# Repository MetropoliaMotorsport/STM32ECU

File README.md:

# ECU for Metropolia Motorsport Team

## Introduction
ECU project is meant to be used in the HPF24 and future cars. 
The project should provide a stable platform for the future development.
## Table of Contents
- [Installation](#installation)
- [Usage](#usage)
- [Contributing](#contributing)
- [Work Rules](##workrules)
- [Changelog](#changelog)
- [License](#license)
- [Acknowledgments](#acknowledgments)
- [Contact](#contact)

## Installation
Clone the project. And import it into the stm32 ide work.
Then build it and upload it to the car ECU using ST-Link.

## Usage
How to use the ECU, with examples.

## Contributing
All development should be done in the `dev` branch.
Create your own branch with your name for the purpose of experimenting and testing.

### Work Rules
1. **Development Branch:** All development should be in the `dev` branch.
2. **Main Branch:** Only working and tested solutions can be merged into `main`.
3. **Experimentation:** For experimenting, create your own branch with your name. You can also use it for development, but changes should be merged to the `dev` first.

## Changelog
History of significant changes.

## License
GPL 3.0 - License

## Acknowledgments
Credits to team members and contributors.

## Contact
Contact information for queries or support.

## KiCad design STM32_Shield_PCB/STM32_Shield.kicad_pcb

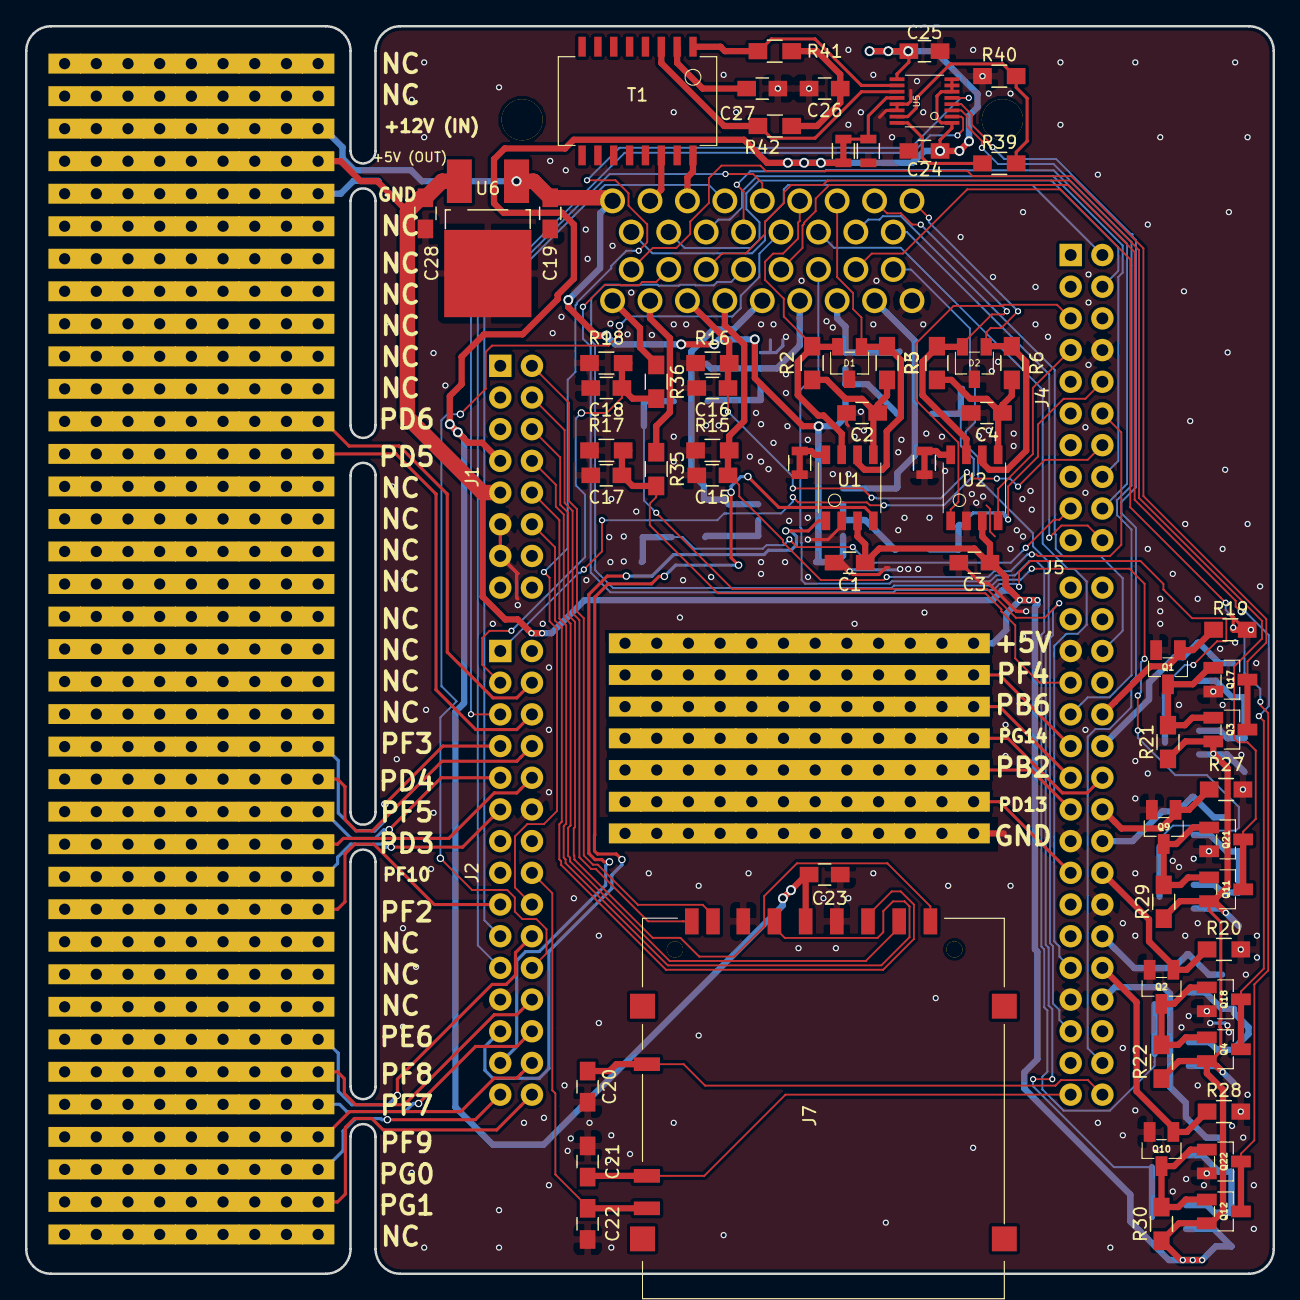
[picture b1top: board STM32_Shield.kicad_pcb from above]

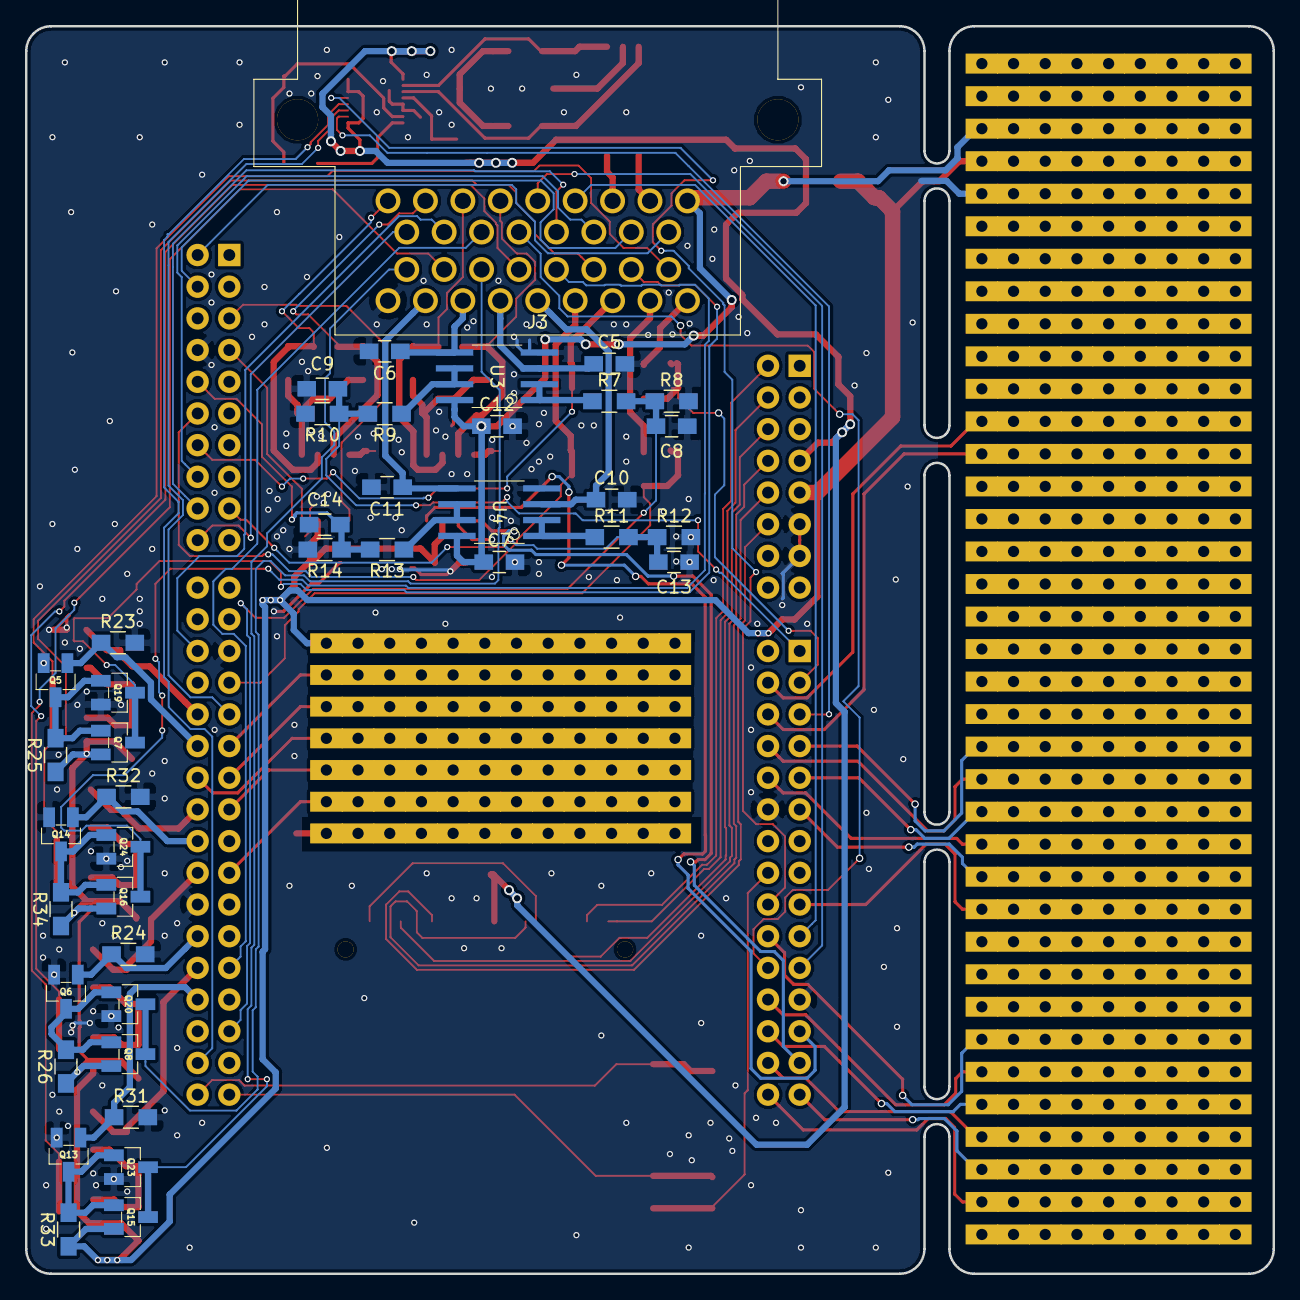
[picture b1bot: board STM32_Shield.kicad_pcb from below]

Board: 2 copper layers, 100.0 x 100.0 mm, 153 parts (41 on the bottom side), 109 nets.

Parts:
C1, C3, C7, C12, C20, C21, C22, C23, C24, C25, C26, C27, C28: 100nF; C_0805_HandSoldering
C2, C4, C5, C6, C8, C9, C10, C11, C13, C14, C15, C16, C17, C18: 4.7nF; C_0805_HandSoldering
C19: 330nF; C_0805_HandSoldering
D1, D2: ESDCAN24-2BLY
J1: Conn_02x08_Odd_Even; 2x08
J2: Conn_02x15_Odd_Even; 2x15
J3: Conn_01x34; SUPERSEAL_34POS
J4: Conn_02x10_Odd_Even; 2x10
J5: Conn_02x17_Odd_Even; 2x17
J6, J15, J16, J17, J18, J19, J20: stripboard_longer
J7: DM1AA
J8, J9, J10, J11, J12, J13, J14, J21, J22, J23, J24, J25, J26, J27, J28, J29, J30, J31, J32, J33, J34, J35, J36, J37, J38, J39, J40, J41, J42, J43, J44, J45, J46, J47, J48, J49, J52: stripboard
Q1, Q2, Q5, Q6, Q9, Q10, Q13, Q14, Q17, Q18, Q19, Q20, Q21, Q22, Q23, Q24: Q_NMOS_GSD; SOT-23
Q3, Q4, Q7, Q8, Q11, Q12, Q15, Q16: Q_PMOS_GSD; SOT-23
R1, R4: 0; jumper
R2, R3, R5, R6, R41, R42: 60; R_0805_HandSoldering
R7, R9, R11, R13: 1.74K; R_0805_HandSoldering
R8, R10, R12, R14, R19, R20, R23, R24, R27, R28, R31, R32: 3.3K; R_0805_HandSoldering
R15, R16: 270; R_0805_HandSoldering
R17, R18, R35, R36: ?; R_0805_HandSoldering
R21, R22, R25, R26, R29, R30, R33, R34: 5.1K; R_0805_HandSoldering
R37: R; jumper
R38: R; R_0805
R39, R40: 1K; R_0805_HandSoldering
T1: HALO_TG110_AEX50N5LF; HALO_N5
U1, U2: TJA1050
U3, U4: LM358; SOIC-8
U5: LTC6820; ltc6820
U6: L7805; TO-252-2_Rectifier

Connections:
+3V3: C23.2, C24.2, C25.2, J1.7, J7.4, R37.1, U5.1, U5.6, U5.7, U5.8, U5.9
+5V: C1.1, C3.1, C28.1, J1.9, J6.1, J12.1, Q3.2, Q4.2, Q7.2, Q8.2, Q11.2, Q12.2, Q15.2, Q16.2, R21.1, R22.1, R25.1, R26.1, R29.1, R30.1, R33.1, R34.1, U1.3, U2.3, U6.3
+12V: C7.1, C12.1, C19.1, J3.26, J10.1, U3.8, U4.8, U6.1
AI0: C5.1, J3.6, U3.3
AI1: C6.1, J3.7, U3.5
AI2: C10.1, J3.5, U4.3
AI3: C11.1, J3.8, U4.5
AI4: C15.1, J3.4, J4.12, R15.1
AI5: C16.1, J3.3, J4.14, R16.1
AI6: J3.2, R35.1
AI7: J3.1, R36.1
CANHI1: D1.2, J3.31, R2.1, U1.7
CANHI2: D2.2, J3.33, R5.1, U2.7
CANLO1: D1.1, J3.32, R3.1, U1.6
CANLO2: D2.1, J3.34, R6.1, U2.6
DI0: J3.18, J4.2
DI1: J3.19, J4.4
DI2: J3.20, J4.16
DI3: J3.21, J4.18
DI4: J2.22, J3.22
DI5: J3.23, J5.25
DI6: J3.24, J5.6
DI7: J3.25, J4.20
DO0: J3.10, Q3.3, Q17.3
DO1: J3.11, Q7.3, Q19.3
DO2: J3.12, Q11.3, Q21.3
DO3: J3.13, Q16.3, Q24.3
DO4: J3.14, Q4.3, Q18.3
DO5: J3.15, Q8.3, Q20.3
DO6: J3.16, Q12.3, Q22.3
DO7: J3.17, Q15.3, Q23.3
GND: C1.2, C2.2, C3.2, C4.2, C5.2, C6.2, C7.2, C8.2, C9.2, C10.2, C11.2, C12.2, C13.2, C14.2, C15.2, C16.2, C17.2, C18.2, C19.2, C20.2, C21.2, C22.2, C23.1, C24.1, C25.1, C26.2, C27.2, C28.2, D1.3, D2.3, J1.11, J1.13, J2.12, J2.23, J3.9, J4.8, J5.5, J5.17, J5.22, J5.27, J7.3, J7.6, J13.1, J20.1, Q1.2, Q2.2, Q5.2, Q6.2, Q9.2, Q10.2, Q13.2, Q14.2, Q17.2, Q18.2, Q19.2, Q20.2, Q21.2, Q22.2, Q23.2, Q24.2, R1.2, R4.2, R8.2, R10.2, R12.2, R14.2, R15.2, R16.2, R17.2, R18.2, R19.2, R20.2, R23.2, R24.2, R27.2, R28.2, R31.2, R32.2, R38.1, R40.1, U1.2, U2.2, U3.4, U4.4, U5.13, U5.14, U6.2
I2C2SCK: J2.19, J3.29
I2C2SDA: J2.21, J3.30
ISOSPI_IM: J3.28, T1.12
ISOSPI_IP: J3.27, T1.10
unnamed: C2.1, R2.2, R3.2, U1.5
unnamed: C4.1, R5.2, R6.2, U2.5
unnamed: C26.1, R41.2, R42.1
unnamed: C27.1, T1.2
unnamed: Q1.3, Q3.1, Q17.1, R21.2
unnamed: Q10.3, Q12.1, Q22.1, R30.2
unnamed: Q9.3, Q11.1, Q21.1, R29.2
unnamed: Q13.3, Q15.1, Q23.1, R33.2
unnamed: Q14.3, Q16.1, Q24.1, R34.2
unnamed: Q2.3, Q4.1, Q18.1, R22.2
unnamed: Q5.3, Q7.1, Q19.1, R25.2
unnamed: Q6.3, Q8.1, Q20.1, R26.2
unnamed: R1.1, U1.8
unnamed: R4.1, U2.8
unnamed: R7.1, U3.1, U3.2
unnamed: R9.1, U3.6, U3.7
unnamed: R11.1, U4.1, U4.2
unnamed: R13.1, U4.6, U4.7
unnamed: R37.2, R38.2, U5.12
unnamed: R39.1, U5.16
unnamed: R39.2, R40.2, U5.15
unnamed: R41.1, T1.1, U5.10
unnamed: R42.2, T1.3, U5.11
PA0: C8.1, J5.29, R7.2, R8.1
PA3: C9.1, J2.1, R9.2, R10.1
PA4: C13.1, J4.17, R11.2, R12.1
PA5: C14.1, J4.10, R13.2, R14.1
PB1: C17.1, J5.7, R17.1, R35.2
PB2: J5.15, J18.1
PB6: J5.13, J16.1
PB10: J5.32, U5.4
PB11: C20.1, J5.34, J7.10
PB12: J4.7, U2.4
PB13: J4.5, U2.1
PC0: C18.1, J2.3, R18.1, R36.2
PC2: J5.9, U5.3
PC3: J2.5, U5.2
PC8: J1.2, J7.7
PC9: J1.4, J7.8
PC10: J1.6, J7.9
PC11: J1.8, J7.1
PC12: J1.10, J7.5
PD0: J2.25, U1.4
PD1: J2.27, U1.1
PD2: J1.12, J7.2
PD3: J2.10, J37.1
PD4: J2.8, J11.1
PD5: J2.6, J27.1
PD6: J2.4, J26.1
PD13: J5.19, J19.1
PE0: C21.1, J5.33, J7.11
PE4: C22.1, J2.16, J7.12
PE5: J2.18, U5.5
PE6: J2.20, J43.1
PE7: J5.20, Q2.1, R20.1
PE8: J5.18, Q14.1, R32.1
PE10: J5.24, Q6.1, R24.1
PE12: J5.26, Q10.1, R28.1
PE13: J5.10, Q1.1, R19.1
PE14: J5.28, Q13.1, R31.1
PF2: J2.17, J39.1
PF3: J2.7, J9.1
PF4: J5.11, J15.1
PF5: J2.9, J36.1
PF7: J2.26, J45.1
PF8: J2.24, J44.1
PF9: J2.28, J46.1
PF10: J2.11, J38.1
PF15: J5.12, Q5.1, R23.1
PG0: J2.29, J47.1
PG1: J2.30, J48.1
PG9: J5.16, Q9.1, R27.1
PG14: J5.14, J17.1

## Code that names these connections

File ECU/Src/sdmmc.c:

/**
  ******************************************************************************
  * File Name          : SDMMC.c
  * Description        : This file provides code for the configuration
  *                      of the SDMMC instances.
  ******************************************************************************
  ** This notice applies to any and all portions of this file
  * that are not between comment pairs USER CODE BEGIN and
  * USER CODE END. Other portions of this file, whether 
  * inserted by the user or by software development tools
  * are owned by their respective copyright owners.
  *
  * COPYRIGHT(c) 2019 STMicroelectronics
  *
  * Redistribution and use in source and binary forms, with or without modification,
  * are permitted provided that the following conditions are met:
  *   1. Redistributions of source code must retain the above copyright notice,
  *      this list of conditions and the following disclaimer.
  *   2. Redistributions in binary form must reproduce the above copyright notice,
  *      this list of conditions and the following disclaimer in the documentation
  *      and/or other materials provided with the distribution.
  *   3. Neither the name of STMicroelectronics nor the names of its contributors
  *      may be used to endorse or promote products derived from this software
  *      without specific prior written permission.
  *
  * THIS SOFTWARE IS PROVIDED BY THE COPYRIGHT HOLDERS AND CONTRIBUTORS "AS IS"
  * AND ANY EXPRESS OR IMPLIED WARRANTIES, INCLUDING, BUT NOT LIMITED TO, THE
  * IMPLIED WARRANTIES OF MERCHANTABILITY AND FITNESS FOR A PARTICULAR PURPOSE ARE
  * DISCLAIMED. IN NO EVENT SHALL THE COPYRIGHT HOLDER OR CONTRIBUTORS BE LIABLE
  * FOR ANY DIRECT, INDIRECT, INCIDENTAL, SPECIAL, EXEMPLARY, OR CONSEQUENTIAL
  * DAMAGES (INCLUDING, BUT NOT LIMITED TO, PROCUREMENT OF SUBSTITUTE GOODS OR
  * SERVICES; LOSS OF USE, DATA, OR PROFITS; OR BUSINESS INTERRUPTION) HOWEVER
  * CAUSED AND ON ANY THEORY OF LIABILITY, WHETHER IN CONTRACT, STRICT LIABILITY,
  * OR TORT (INCLUDING NEGLIGENCE OR OTHERWISE) ARISING IN ANY WAY OUT OF THE USE
  * OF THIS SOFTWARE, EVEN IF ADVISED OF THE POSSIBILITY OF SUCH DAMAGE.
  *
  ******************************************************************************
  */

/* Includes ------------------------------------------------------------------*/
#include "sdmmc.h"

/* USER CODE BEGIN 0 */

/* USER CODE END 0 */

SD_HandleTypeDef hsd1;

/* SDMMC1 init function */

void MX_SDMMC1_SD_Init(void)
{

  hsd1.Instance = SDMMC1;
  hsd1.Init.ClockEdge = SDMMC_CLOCK_EDGE_RISING;
  hsd1.Init.ClockPowerSave = SDMMC_CLOCK_POWER_SAVE_DISABLE;
  hsd1.Init.BusWide = SDMMC_BUS_WIDE_4B;
  hsd1.Init.HardwareFlowControl = SDMMC_HARDWARE_FLOW_CONTROL_DISABLE;
  hsd1.Init.ClockDiv = 0;
  if (HAL_SD_Init(&hsd1) != HAL_OK)
  {
    Error_Handler();
  }

}

void HAL_SD_MspInit(SD_HandleTypeDef* sdHandle)
{

  GPIO_InitTypeDef GPIO_InitStruct = {0};
  if(sdHandle->Instance==SDMMC1)
  {
  /* USER CODE BEGIN SDMMC1_MspInit 0 */

  /* USER CODE END SDMMC1_MspInit 0 */
    /* SDMMC1 clock enable */
    __HAL_RCC_SDMMC1_CLK_ENABLE();
  
    __HAL_RCC_GPIOC_CLK_ENABLE();
    __HAL_RCC_GPIOD_CLK_ENABLE();
    /**SDMMC1 GPIO Configuration    
    PC8     ------> SDMMC1_D0
    PC9     ------> SDMMC1_D1
    PC10     ------> SDMMC1_D2
    PC11     ------> SDMMC1_D3
    PC12     ------> SDMMC1_CK
    PD2     ------> SDMMC1_CMD 
    */
    GPIO_InitStruct.Pin = GPIO_PIN_8|GPIO_PIN_9|GPIO_PIN_10|GPIO_PIN_11 
                          |GPIO_PIN_12;
    GPIO_InitStruct.Mode = GPIO_MODE_AF_PP;
    GPIO_InitStruct.Pull = GPIO_NOPULL;
    GPIO_InitStruct.Speed = GPIO_SPEED_FREQ_VERY_HIGH;
    GPIO_InitStruct.Alternate = GPIO_AF12_SDIO1;
    HAL_GPIO_Init(GPIOC, &GPIO_InitStruct);

    GPIO_InitStruct.Pin = GPIO_PIN_2;
    GPIO_InitStruct.Mode = GPIO_MODE_AF_PP;
    GPIO_InitStruct.Pull = GPIO_NOPULL;
    GPIO_InitStruct.Speed = GPIO_SPEED_FREQ_VERY_HIGH;
    GPIO_InitStruct.Alternate = GPIO_AF12_SDIO1;
    HAL_GPIO_Init(GPIOD, &GPIO_InitStruct);

  /* USER CODE BEGIN SDMMC1_MspInit 1 */

  /* USER CODE END SDMMC1_MspInit 1 */
  }
}

void HAL_SD_MspDeInit(SD_HandleTypeDef* sdHandle)
{

  if(sdHandle->Instance==SDMMC1)
  {
  /* USER CODE BEGIN SDMMC1_MspDeInit 0 */

  /* USER CODE END SDMMC1_MspDeInit 0 */
    /* Peripheral clock disable */
    __HAL_RCC_SDMMC1_CLK_DISABLE();
  
    /**SDMMC1 GPIO Configuration    
    PC8     ------> SDMMC1_D0
    PC9     ------> SDMMC1_D1
    PC10     ------> SDMMC1_D2
    PC11     ------> SDMMC1_D3
    PC12     ------> SDMMC1_CK
    PD2     ------> SDMMC1_CMD 
    */
    HAL_GPIO_DeInit(GPIOC, GPIO_PIN_8|GPIO_PIN_9|GPIO_PIN_10|GPIO_PIN_11 
                          |GPIO_PIN_12);

    HAL_GPIO_DeInit(GPIOD, GPIO_PIN_2);

  /* USER CODE BEGIN SDMMC1_MspDeInit 1 */

  /* USER CODE END SDMMC1_MspDeInit 1 */
  }
} 

/* USER CODE BEGIN 1 */

/* USER CODE END 1 */

/************************ (C) COPYRIGHT STMicroelectronics *****END OF FILE****/

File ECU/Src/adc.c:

/**
  ******************************************************************************
  * File Name          : ADC.c
  * Description        : This file provides code for the configuration
  *                      of the ADC instances.
  ******************************************************************************
  ** This notice applies to any and all portions of this file
  * that are not between comment pairs USER CODE BEGIN and
  * USER CODE END. Other portions of this file, whether 
  * inserted by the user or by software development tools
  * are owned by their respective copyright owners.
  *
  * COPYRIGHT(c) 2019 STMicroelectronics
  *
  * Redistribution and use in source and binary forms, with or without modification,
  * are permitted provided that the following conditions are met:
  *   1. Redistributions of source code must retain the above copyright notice,
  *      this list of conditions and the following disclaimer.
  *   2. Redistributions in binary form must reproduce the above copyright notice,
  *      this list of conditions and the following disclaimer in the documentation
  *      and/or other materials provided with the distribution.
  *   3. Neither the name of STMicroelectronics nor the names of its contributors
  *      may be used to endorse or promote products derived from this software
  *      without specific prior written permission.
  *
  * THIS SOFTWARE IS PROVIDED BY THE COPYRIGHT HOLDERS AND CONTRIBUTORS "AS IS"
  * AND ANY EXPRESS OR IMPLIED WARRANTIES, INCLUDING, BUT NOT LIMITED TO, THE
  * IMPLIED WARRANTIES OF MERCHANTABILITY AND FITNESS FOR A PARTICULAR PURPOSE ARE
  * DISCLAIMED. IN NO EVENT SHALL THE COPYRIGHT HOLDER OR CONTRIBUTORS BE LIABLE
  * FOR ANY DIRECT, INDIRECT, INCIDENTAL, SPECIAL, EXEMPLARY, OR CONSEQUENTIAL
  * DAMAGES (INCLUDING, BUT NOT LIMITED TO, PROCUREMENT OF SUBSTITUTE GOODS OR
  * SERVICES; LOSS OF USE, DATA, OR PROFITS; OR BUSINESS INTERRUPTION) HOWEVER
  * CAUSED AND ON ANY THEORY OF LIABILITY, WHETHER IN CONTRACT, STRICT LIABILITY,
  * OR TORT (INCLUDING NEGLIGENCE OR OTHERWISE) ARISING IN ANY WAY OUT OF THE USE
  * OF THIS SOFTWARE, EVEN IF ADVISED OF THE POSSIBILITY OF SUCH DAMAGE.
  *
  ******************************************************************************
  */

/* Includes ------------------------------------------------------------------*/
#include "adc.h"

/* USER CODE BEGIN 0 */

/* USER CODE END 0 */

ADC_HandleTypeDef hadc1;
DMA_HandleTypeDef hdma_adc1;

/* ADC1 init function */
void MX_ADC1_Init(void)
{
  ADC_MultiModeTypeDef multimode = {0};
  ADC_ChannelConfTypeDef sConfig = {0};

  /**Common config 
  */
  hadc1.Instance = ADC1;
  hadc1.Init.ClockPrescaler = ADC_CLOCK_ASYNC_DIV6;
  hadc1.Init.Resolution = ADC_RESOLUTION_16B;
  hadc1.Init.ScanConvMode = ADC_SCAN_ENABLE;
  hadc1.Init.EOCSelection = ADC_EOC_SINGLE_CONV;
  hadc1.Init.LowPowerAutoWait = DISABLE;
  hadc1.Init.ContinuousConvMode = ENABLE;
  hadc1.Init.NbrOfConversion = 8;
  hadc1.Init.DiscontinuousConvMode = DISABLE;
  hadc1.Init.ExternalTrigConv = ADC_SOFTWARE_START;
  hadc1.Init.ExternalTrigConvEdge = ADC_EXTERNALTRIGCONVEDGE_NONE;
  hadc1.Init.ConversionDataManagement = ADC_CONVERSIONDATA_DMA_CIRCULAR;
  hadc1.Init.Overrun = ADC_OVR_DATA_OVERWRITTEN;
  hadc1.Init.LeftBitShift = ADC_LEFTBITSHIFT_NONE;
  hadc1.Init.BoostMode = DISABLE;
  hadc1.Init.OversamplingMode = DISABLE;
  if (HAL_ADC_Init(&hadc1) != HAL_OK)
  {
    Error_Handler();
  }
  /**Configure the ADC multi-mode 
  */
  multimode.Mode = ADC_MODE_INDEPENDENT;
  if (HAL_ADCEx_MultiModeConfigChannel(&hadc1, &multimode) != HAL_OK)
  {
    Error_Handler();
  }
  /**Configure Regular Channel 
  */
  sConfig.Channel = ADC_CHANNEL_15;
  sConfig.Rank = ADC_REGULAR_RANK_1;
  sConfig.SamplingTime = ADC_SAMPLETIME_64CYCLES_5;
  sConfig.SingleDiff = ADC_SINGLE_ENDED;
  sConfig.OffsetNumber = ADC_OFFSET_NONE;
  sConfig.Offset = 0;
  if (HAL_ADC_ConfigChannel(&hadc1, &sConfig) != HAL_OK)
  {
    Error_Handler();
  }
  /**Configure Regular Channel 
  */
  sConfig.Channel = ADC_CHANNEL_10;
  sConfig.Rank = ADC_REGULAR_RANK_2;
  if (HAL_ADC_ConfigChannel(&hadc1, &sConfig) != HAL_OK)
  {
    Error_Handler();
  }
  /**Configure Regular Channel 
  */
  sConfig.Channel = ADC_CHANNEL_19;
  sConfig.Rank = ADC_REGULAR_RANK_3;
  sConfig.SamplingTime = ADC_SAMPLETIME_387CYCLES_5;
  if (HAL_ADC_ConfigChannel(&hadc1, &sConfig) != HAL_OK)
  {
    Error_Handler();
  }
  /**Configure Regular Channel 
  */
  sConfig.Channel = ADC_CHANNEL_3;
  sConfig.Rank = ADC_REGULAR_RANK_4;
  if (HAL_ADC_ConfigChannel(&hadc1, &sConfig) != HAL_OK)
  {
    Error_Handler();
  }
  /**Configure Regular Channel 
  */
  sConfig.Channel = ADC_CHANNEL_7;
  sConfig.Rank = ADC_REGULAR_RANK_5;
  if (HAL_ADC_ConfigChannel(&hadc1, &sConfig) != HAL_OK)
  {
    Error_Handler();
  }
  /**Configure Regular Channel 
  */
  sConfig.Channel = ADC_CHANNEL_18;
  sConfig.Rank = ADC_REGULAR_RANK_6;
  if (HAL_ADC_ConfigChannel(&hadc1, &sConfig) != HAL_OK)
  {
    Error_Handler();
  }
  /**Configure Regular Channel 
  */
  sConfig.Channel = ADC_CHANNEL_5;
  sConfig.Rank = ADC_REGULAR_RANK_7;
  if (HAL_ADC_ConfigChannel(&hadc1, &sConfig) != HAL_OK)
  {
    Error_Handler();
  }
  /**Configure Regular Channel 
  */
  sConfig.Channel = ADC_CHANNEL_16;
  sConfig.Rank = ADC_REGULAR_RANK_8;
  if (HAL_ADC_ConfigChannel(&hadc1, &sConfig) != HAL_OK)
  {
    Error_Handler();
  }

}

void HAL_ADC_MspInit(ADC_HandleTypeDef* adcHandle)
{

  GPIO_InitTypeDef GPIO_InitStruct = {0};
  if(adcHandle->Instance==ADC1)
  {
  /* USER CODE BEGIN ADC1_MspInit 0 */

  /* USER CODE END ADC1_MspInit 0 */
    /* ADC1 clock enable */
    __HAL_RCC_ADC12_CLK_ENABLE();
  
    __HAL_RCC_GPIOC_CLK_ENABLE();
    __HAL_RCC_GPIOA_CLK_ENABLE();
    __HAL_RCC_GPIOB_CLK_ENABLE();
    __HAL_RCC_GPIOF_CLK_ENABLE();
    /**ADC1 GPIO Configuration    
    PC0     ------> ADC1_INP10
    PA0     ------> ADC1_INP16
    PA3     ------> ADC1_INP15
    PA4     ------> ADC1_INP18
    PA5     ------> ADC1_INP19
    PA6     ------> ADC1_INP3
    PA7     ------> ADC1_INP7
    PB1     ------> ADC1_INP5
    PF12     ------> ADC1_INP6 
    */
    GPIO_InitStruct.Pin = GPIO_PIN_0;
    GPIO_InitStruct.Mode = GPIO_MODE_ANALOG;
    GPIO_InitStruct.Pull = GPIO_NOPULL;
    HAL_GPIO_Init(GPIOC, &GPIO_InitStruct);

    GPIO_InitStruct.Pin = GPIO_PIN_0|GPIO_PIN_3|GPIO_PIN_4|GPIO_PIN_5 
                          |GPIO_PIN_6|GPIO_PIN_7;
    GPIO_InitStruct.Mode = GPIO_MODE_ANALOG;
    GPIO_InitStruct.Pull = GPIO_NOPULL;
    HAL_GPIO_Init(GPIOA, &GPIO_InitStruct);

    GPIO_InitStruct.Pin = GPIO_PIN_1;
    GPIO_InitStruct.Mode = GPIO_MODE_ANALOG;
    GPIO_InitStruct.Pull = GPIO_NOPULL;
    HAL_GPIO_Init(GPIOB, &GPIO_InitStruct);

    GPIO_InitStruct.Pin = GPIO_PIN_12;
    GPIO_InitStruct.Mode = GPIO_MODE_ANALOG;
    GPIO_InitStruct.Pull = GPIO_NOPULL;
    HAL_GPIO_Init(GPIOF, &GPIO_InitStruct);

    /* ADC1 DMA Init */
    /* ADC1 Init */
    hdma_adc1.Instance = DMA1_Stream0;
    hdma_adc1.Init.Request = DMA_REQUEST_ADC1;
    hdma_adc1.Init.Direction = DMA_PERIPH_TO_MEMORY;
    hdma_adc1.Init.PeriphInc = DMA_PINC_DISABLE;
    hdma_adc1.Init.MemInc = DMA_MINC_ENABLE;
    hdma_adc1.Init.PeriphDataAlignment = DMA_PDATAALIGN_WORD;
    hdma_adc1.Init.MemDataAlignment = DMA_MDATAALIGN_WORD;
    hdma_adc1.Init.Mode = DMA_CIRCULAR;
    hdma_adc1.Init.Priority = DMA_PRIORITY_HIGH;
    hdma_adc1.Init.FIFOMode = DMA_FIFOMODE_DISABLE;
    if (HAL_DMA_Init(&hdma_adc1) != HAL_OK)
    {
      Error_Handler();
    }

    __HAL_LINKDMA(adcHandle,DMA_Handle,hdma_adc1);

  /* USER CODE BEGIN ADC1_MspInit 1 */

  /* USER CODE END ADC1_MspInit 1 */
  }
}

void HAL_ADC_MspDeInit(ADC_HandleTypeDef* adcHandle)
{

  if(adcHandle->Instance==ADC1)
  {
  /* USER CODE BEGIN ADC1_MspDeInit 0 */

  /* USER CODE END ADC1_MspDeInit 0 */
    /* Peripheral clock disable */
    __HAL_RCC_ADC12_CLK_DISABLE();
  
    /**ADC1 GPIO Configuration    
    PC0     ------> ADC1_INP10
    PA0     ------> ADC1_INP16
    PA3     ------> ADC1_INP15
    PA4     ------> ADC1_INP18
    PA5     ------> ADC1_INP19
    PA6     ------> ADC1_INP3
    PA7     ------> ADC1_INP7
    PB1     ------> ADC1_INP5
    PF12     ------> ADC1_INP6 
    */
    HAL_GPIO_DeInit(GPIOC, GPIO_PIN_0);

    HAL_GPIO_DeInit(GPIOA, GPIO_PIN_0|GPIO_PIN_3|GPIO_PIN_4|GPIO_PIN_5 
                          |GPIO_PIN_6|GPIO_PIN_7);

    HAL_GPIO_DeInit(GPIOB, GPIO_PIN_1);

    HAL_GPIO_DeInit(GPIOF, GPIO_PIN_12);

    /* ADC1 DMA DeInit */
    HAL_DMA_DeInit(adcHandle->DMA_Handle);
  /* USER CODE BEGIN ADC1_MspDeInit 1 */

  /* USER CODE END ADC1_MspDeInit 1 */
  }
} 

/* USER CODE BEGIN 1 */

/* USER CODE END 1 */

/************************ (C) COPYRIGHT STMicroelectronics *****END OF FILE****/

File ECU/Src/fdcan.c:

/**
  ******************************************************************************
  * File Name          : FDCAN.c
  * Description        : This file provides code for the configuration
  *                      of the FDCAN instances.
  ******************************************************************************
  ** This notice applies to any and all portions of this file
  * that are not between comment pairs USER CODE BEGIN and
  * USER CODE END. Other portions of this file, whether 
  * inserted by the user or by software development tools
  * are owned by their respective copyright owners.
  *
  * COPYRIGHT(c) 2019 STMicroelectronics
  *
  * Redistribution and use in source and binary forms, with or without modification,
  * are permitted provided that the following conditions are met:
  *   1. Redistributions of source code must retain the above copyright notice,
  *      this list of conditions and the following disclaimer.
  *   2. Redistributions in binary form must reproduce the above copyright notice,
  *      this list of conditions and the following disclaimer in the documentation
  *      and/or other materials provided with the distribution.
  *   3. Neither the name of STMicroelectronics nor the names of its contributors
  *      may be used to endorse or promote products derived from this software
  *      without specific prior written permission.
  *
  * THIS SOFTWARE IS PROVIDED BY THE COPYRIGHT HOLDERS AND CONTRIBUTORS "AS IS"
  * AND ANY EXPRESS OR IMPLIED WARRANTIES, INCLUDING, BUT NOT LIMITED TO, THE
  * IMPLIED WARRANTIES OF MERCHANTABILITY AND FITNESS FOR A PARTICULAR PURPOSE ARE
  * DISCLAIMED. IN NO EVENT SHALL THE COPYRIGHT HOLDER OR CONTRIBUTORS BE LIABLE
  * FOR ANY DIRECT, INDIRECT, INCIDENTAL, SPECIAL, EXEMPLARY, OR CONSEQUENTIAL
  * DAMAGES (INCLUDING, BUT NOT LIMITED TO, PROCUREMENT OF SUBSTITUTE GOODS OR
  * SERVICES; LOSS OF USE, DATA, OR PROFITS; OR BUSINESS INTERRUPTION) HOWEVER
  * CAUSED AND ON ANY THEORY OF LIABILITY, WHETHER IN CONTRACT, STRICT LIABILITY,
  * OR TORT (INCLUDING NEGLIGENCE OR OTHERWISE) ARISING IN ANY WAY OUT OF THE USE
  * OF THIS SOFTWARE, EVEN IF ADVISED OF THE POSSIBILITY OF SUCH DAMAGE.
  *
  ******************************************************************************
  */

/* Includes ------------------------------------------------------------------*/
#include "fdcan.h"

/* USER CODE BEGIN 0 */

/* USER CODE END 0 */

FDCAN_HandleTypeDef hfdcan1;
FDCAN_HandleTypeDef hfdcan2;

/* FDCAN1 init function */
void MX_FDCAN1_Init(void)
{

  hfdcan1.Instance = FDCAN1;
  hfdcan1.Init.FrameFormat = FDCAN_FRAME_CLASSIC;
  hfdcan1.Init.Mode = FDCAN_MODE_NORMAL;
  hfdcan1.Init.AutoRetransmission = DISABLE;
  hfdcan1.Init.TransmitPause = DISABLE;
  hfdcan1.Init.NominalPrescaler = 4;
  hfdcan1.Init.NominalSyncJumpWidth = 20;
  hfdcan1.Init.NominalTimeSeg1 = 14;
  hfdcan1.Init.NominalTimeSeg2 = 5;
  hfdcan1.Init.DataPrescaler = 1;
  hfdcan1.Init.DataSyncJumpWidth = 1;
  hfdcan1.Init.DataTimeSeg1 = 1;
  hfdcan1.Init.DataTimeSeg2 = 1;
  hfdcan1.Init.MessageRAMOffset = 0;
  hfdcan1.Init.StdFiltersNbr = 128;
  hfdcan1.Init.ExtFiltersNbr = 0;
  hfdcan1.Init.RxFifo0ElmtsNbr = 32;
  hfdcan1.Init.RxFifo0ElmtSize = FDCAN_DATA_BYTES_8;
  hfdcan1.Init.RxFifo1ElmtsNbr = 32;
  hfdcan1.Init.RxFifo1ElmtSize = FDCAN_DATA_BYTES_8;
  hfdcan1.Init.RxBuffersNbr = 0;
  hfdcan1.Init.RxBufferSize = FDCAN_DATA_BYTES_8;
  hfdcan1.Init.TxEventsNbr = 0;
  hfdcan1.Init.TxBuffersNbr = 0;
  hfdcan1.Init.TxFifoQueueElmtsNbr = 32;
  hfdcan1.Init.TxFifoQueueMode = FDCAN_TX_FIFO_OPERATION;
  hfdcan1.Init.TxElmtSize = FDCAN_DATA_BYTES_8;
  hfdcan1.msgRam.StandardFilterSA = 0;
  hfdcan1.msgRam.ExtendedFilterSA = 0;
  hfdcan1.msgRam.RxFIFO0SA = 0;
  hfdcan1.msgRam.RxFIFO1SA = 0;
  hfdcan1.msgRam.RxBufferSA = 0;
  hfdcan1.msgRam.TxEventFIFOSA = 0;
  hfdcan1.msgRam.TxBufferSA = 0;
  hfdcan1.msgRam.TxFIFOQSA = 0;
  hfdcan1.msgRam.TTMemorySA = 0;
  hfdcan1.msgRam.EndAddress = 0;
  hfdcan1.ErrorCode = 0;
  if (HAL_FDCAN_Init(&hfdcan1) != HAL_OK)
  {
    Error_Handler();
  }

}
/* FDCAN2 init function */
void MX_FDCAN2_Init(void)
{

  hfdcan2.Instance = FDCAN2;
  hfdcan2.Init.FrameFormat = FDCAN_FRAME_CLASSIC;
  hfdcan2.Init.Mode = FDCAN_MODE_NORMAL;
  hfdcan2.Init.AutoRetransmission = DISABLE;
  hfdcan2.Init.TransmitPause = DISABLE;
  hfdcan2.Init.NominalPrescaler = 4;
  hfdcan2.Init.NominalSyncJumpWidth = 20;
  hfdcan2.Init.NominalTimeSeg1 = 14;
  hfdcan2.Init.NominalTimeSeg2 = 5;
  hfdcan2.Init.DataPrescaler = 1;
  hfdcan2.Init.DataSyncJumpWidth = 1;
  hfdcan2.Init.DataTimeSeg1 = 1;
  hfdcan2.Init.DataTimeSeg2 = 1;
  hfdcan2.Init.MessageRAMOffset = 0;
  hfdcan2.Init.StdFiltersNbr = 128;
  hfdcan2.Init.ExtFiltersNbr = 0;
  hfdcan2.Init.RxFifo0ElmtsNbr = 32;
  hfdcan2.Init.RxFifo0ElmtSize = FDCAN_DATA_BYTES_8;
  hfdcan2.Init.RxFifo1ElmtsNbr = 32;
  hfdcan2.Init.RxFifo1ElmtSize = FDCAN_DATA_BYTES_8;
  hfdcan2.Init.RxBuffersNbr = 0;
  hfdcan2.Init.RxBufferSize = FDCAN_DATA_BYTES_8;
  hfdcan2.Init.TxEventsNbr = 0;
  hfdcan2.Init.TxBuffersNbr = 0;
  hfdcan2.Init.TxFifoQueueElmtsNbr = 32;
  hfdcan2.Init.TxFifoQueueMode = FDCAN_TX_FIFO_OPERATION;
  hfdcan2.Init.TxElmtSize = FDCAN_DATA_BYTES_8;
  hfdcan2.msgRam.StandardFilterSA = 0;
  hfdcan2.msgRam.ExtendedFilterSA = 0;
  hfdcan2.msgRam.RxFIFO0SA = 0;
  hfdcan2.msgRam.RxFIFO1SA = 0;
  hfdcan2.msgRam.RxBufferSA = 0;
  hfdcan2.msgRam.TxEventFIFOSA = 0;
  hfdcan2.msgRam.TxBufferSA = 0;
  hfdcan2.msgRam.TxFIFOQSA = 0;
  hfdcan2.msgRam.TTMemorySA = 0;
  hfdcan2.msgRam.EndAddress = 0;
  hfdcan2.ErrorCode = 0;
  if (HAL_FDCAN_Init(&hfdcan2) != HAL_OK)
  {
    Error_Handler();
  }

}

static uint32_t HAL_RCC_FDCAN_CLK_ENABLED=0;

void HAL_FDCAN_MspInit(FDCAN_HandleTypeDef* fdcanHandle)
{

  GPIO_InitTypeDef GPIO_InitStruct = {0};
  if(fdcanHandle->Instance==FDCAN1)
  {
  /* USER CODE BEGIN FDCAN1_MspInit 0 */

  /* USER CODE END FDCAN1_MspInit 0 */
    /* FDCAN1 clock enable */
    HAL_RCC_FDCAN_CLK_ENABLED++;
    if(HAL_RCC_FDCAN_CLK_ENABLED==1){
      __HAL_RCC_FDCAN_CLK_ENABLE();
    }
  
    __HAL_RCC_GPIOD_CLK_ENABLE();
    /**FDCAN1 GPIO Configuration    
    PD0     ------> FDCAN1_RX
    PD1     ------> FDCAN1_TX 
    */
    GPIO_InitStruct.Pin = GPIO_PIN_0|GPIO_PIN_1;
    GPIO_InitStruct.Mode = GPIO_MODE_AF_PP;
    GPIO_InitStruct.Pull = GPIO_NOPULL;
    GPIO_InitStruct.Speed = GPIO_SPEED_FREQ_LOW;
    GPIO_InitStruct.Alternate = GPIO_AF9_FDCAN1;
    HAL_GPIO_Init(GPIOD, &GPIO_InitStruct);

    /* FDCAN1 interrupt Init */
    HAL_NVIC_SetPriority(FDCAN1_IT0_IRQn, 0, 0);
    HAL_NVIC_EnableIRQ(FDCAN1_IT0_IRQn);
  /* USER CODE BEGIN FDCAN1_MspInit 1 */

  /* USER CODE END FDCAN1_MspInit 1 */
  }
  else if(fdcanHandle->Instance==FDCAN2)
  {
  /* USER CODE BEGIN FDCAN2_MspInit 0 */

  /* USER CODE END FDCAN2_MspInit 0 */
    /* FDCAN2 clock enable */
    HAL_RCC_FDCAN_CLK_ENABLED++;
    if(HAL_RCC_FDCAN_CLK_ENABLED==1){
      __HAL_RCC_FDCAN_CLK_ENABLE();
    }
  
    __HAL_RCC_GPIOB_CLK_ENABLE();
    /**FDCAN2 GPIO Configuration    
    PB12     ------> FDCAN2_RX
    PB13     ------> FDCAN2_TX 
    */
    GPIO_InitStruct.Pin = GPIO_PIN_12|GPIO_PIN_13;
    GPIO_InitStruct.Mode = GPIO_MODE_AF_PP;
    GPIO_InitStruct.Pull = GPIO_NOPULL;
    GPIO_InitStruct.Speed = GPIO_SPEED_FREQ_LOW;
    GPIO_InitStruct.Alternate = GPIO_AF9_FDCAN2;
    HAL_GPIO_Init(GPIOB, &GPIO_InitStruct);

    /* FDCAN2 interrupt Init */
    HAL_NVIC_SetPriority(FDCAN2_IT0_IRQn, 0, 0);
    HAL_NVIC_EnableIRQ(FDCAN2_IT0_IRQn);
  /* USER CODE BEGIN FDCAN2_MspInit 1 */

  /* USER CODE END FDCAN2_MspInit 1 */
  }
}

void HAL_FDCAN_MspDeInit(FDCAN_HandleTypeDef* fdcanHandle)
{

  if(fdcanHandle->Instance==FDCAN1)
  {
  /* USER CODE BEGIN FDCAN1_MspDeInit 0 */

  /* USER CODE END FDCAN1_MspDeInit 0 */
    /* Peripheral clock disable */
    HAL_RCC_FDCAN_CLK_ENABLED--;
    if(HAL_RCC_FDCAN_CLK_ENABLED==0){
      __HAL_RCC_FDCAN_CLK_DISABLE();
    }
  
    /**FDCAN1 GPIO Configuration    
    PD0     ------> FDCAN1_RX
    PD1     ------> FDCAN1_TX 
    */
    HAL_GPIO_DeInit(GPIOD, GPIO_PIN_0|GPIO_PIN_1);

    /* FDCAN1 interrupt Deinit */
    HAL_NVIC_DisableIRQ(FDCAN1_IT0_IRQn);
  /* USER CODE BEGIN FDCAN1_MspDeInit 1 */

  /* USER CODE END FDCAN1_MspDeInit 1 */
  }
  else if(fdcanHandle->Instance==FDCAN2)
  {
  /* USER CODE BEGIN FDCAN2_MspDeInit 0 */

  /* USER CODE END FDCAN2_MspDeInit 0 */
    /* Peripheral clock disable */
    HAL_RCC_FDCAN_CLK_ENABLED--;
    if(HAL_RCC_FDCAN_CLK_ENABLED==0){
      __HAL_RCC_FDCAN_CLK_DISABLE();
    }
  
    /**FDCAN2 GPIO Configuration    
    PB12     ------> FDCAN2_RX
    PB13     ------> FDCAN2_TX 
    */
    HAL_GPIO_DeInit(GPIOB, GPIO_PIN_12|GPIO_PIN_13);

    /* FDCAN2 interrupt Deinit */
    HAL_NVIC_DisableIRQ(FDCAN2_IT0_IRQn);
  /* USER CODE BEGIN FDCAN2_MspDeInit 1 */

  /* USER CODE END FDCAN2_MspDeInit 1 */
  }
} 

/* USER CODE BEGIN 1 */

/* USER CODE END 1 */

/************************ (C) COPYRIGHT STMicroelectronics *****END OF FILE****/

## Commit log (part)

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2022-06-09 Drop to error state from running state if HV is lost.
2022-06-13 reverse steering angle positive direction.
2022-06-14 Simplify HV lost check.
2022-06-17 Change vectoring output
2022-06-18 Changed TCS system output to right one all should be subtracting
2022-06-19 Start adding in matlab regen code.
2022-06-19 add vscode to gitignore
2022-06-19 Wire in more of matlab regen calc
2022-06-19 fix typo
2022-06-19 disable uart screen
2022-06-19 Debug led tests, disable error state shutdown circuit check.
    Disable uart input and lcd stuff.
2022-06-20 TV yawmoment fix
2022-06-22 Add matlab regen take 2
2022-06-22 Disable SDC check to allow error state exit for now
2022-06-22 Add matlab regen control code
2022-06-23 disable led debug in output task
2022-06-23 inverter global regen set by carstate
2022-07-01 Update default power on devices and node 37 channels.
2022-07-04 Clarify error state clear message.
2022-07-04 node changes
2022-07-21 Prevent restart from error state
2022-07-22 Use immiediete LED state change for TSOFF and IMD LED's
2022-07-22 direct output on setoutputnow
2022-07-22 missed commenting out
2022-07-22 AMS led on bms timeout.
2022-07-22 more AMS light stuff.
2022-07-22 fix AMS led state
2022-07-22 totally disable leaving error state.
2022-07-22 don't allow re entering TS state after precharge complete
2022-07-22 move from precharge to enering ts active state
2022-07-22 require full power cycle after TS has been on to restart.
2022-07-22 Disable more AMS light controls.
2022-07-22 Revert "Disable more AMS light controls."
    This reverts commit 5530174c0ab221090558790bdf5c6696c444eb7e.
2022-07-22 Revert "fix AMS led state"
    This reverts commit 9ff4b05da091937e12f5f53ab278e69e63b0f0b6.
2022-07-22 Revert "more AMS light stuff."
    This reverts commit 21e6d2de4b93ca1e5daed343a3b54ca7b6fbe037.
2022-07-22 Revert "AMS led on bms timeout."
    This reverts commit 1b781db186d02a2d338864ae4f56cb2c0e9180e4.
2022-07-22 Revert "Set AMS light from BMS message."
    This reverts commit 4a70228f9dc55a66aa0ac045ee1def2bd1372bd9.
2022-07-22 BMS Led control from powertask.
2022-07-22 Remove old LED time test.
2022-07-22 check bms function
2022-07-22 fix func definition
2022-07-22 BMS message control.
2022-07-22 BMS light from timeout message.
2022-07-22 set BMS state after LED test.
2022-08-06 Direct bypass tv if throttle input under 10%
2022-08-06 Updated code to working rpmmaxrR
2022-08-06 Update torque req % scaling from 0-100 to 0-1
2022-08-13 Update LED code to simpler model, task avoids que, just checks and updates states every cycle.
2022-08-17 LED output fixes.
2022-08-17 Revert torque control 10% check
2022-08-17 Remove back1 power request for TSAL
    TSAL dropping power after power on if back 1 powered.
2022-08-17 cleanup more led settings.
2022-08-18 Stop TSOFF blinking hopefully
2022-08-18 voltage test attempt in ts process
2022-08-19 TSOff monitoring light message
2022-08-19 Flag critical error correctly.
2022-08-20 Restore critical error checking, fix some includes, fix regen matlab call format
2022-08-20 Idle process solid light timer.
2022-09-05 fix inverter numbering
2022-09-05 Fix doregen call to not pass pedal percentage
2022-09-05 Only adjust torque values if torque_request not zero.
2022-09-08 added 18nm
2022-09-08 missing Critical error variable restored
2022-09-09 Add AppsR bodge possibility
2022-09-10 make analogue node 1 easier to differentiate from 11
2022-09-10 Torque vectoring output adjustment was ignoring initial balance calculation.
2022-09-18 Change APPC config done from error to status msg.
2023-03-07 return immediately from wheel button read if zero data
2023-04-05 Add a calibrated based physical max cut off beyond which readings will fail sanity check
2023-05-31 Setup inverters for front/back motor control instead of left/right for 2023
2023-06-16 Add wheel input debug messages for testing
2023-06-18 Add RTT debug output, fixes to wheel read code.
2023-06-21 ECU wheel input reading, interrupt triggered
2023-06-21 wheel interrupt handling
2023-06-21 Add RTT for debug purposes, and bench setup
2023-06-21 Allow display function again
2023-06-29 Config powernode 37 for hpf2023
2023-07-01 TSAL channel moved on node 37
2023-07-01 highest cellV reading for regen control, new BMS SOC msg
2023-07-02 updates for HPF2023 BMS message
2023-07-02 bms msg debug message test
2023-07-02 Ignore some nodes ifndef HPF2023
2023-07-02 Fix bms message read bytes and endianness.
2023-07-02 Only check for power nodes 34 and 37
2023-07-02 add critical error code
2023-07-02 Restore powernodes 35 and 36, 36 to inv bus
2023-07-02 Tidy up power node, check POWERNODECOUNT direct from array.
2023-07-02 Fix pnode 37 DLC, remove Back1 define
2023-07-02 Power handling simplification
2023-07-02 Fix device power status list
2023-07-02 Add analogue critical direct debug
2023-07-03 Debug config menu test
2023-07-03 Ignore first wheel interrupt if no reply
2023-07-03 Move fan channels on n35 from 2-3 to 0-1
2023-07-03 unflag redraw at end of menu cycle
2023-07-03 disable brakelight control for testing
2023-07-03 Update a11 for new brake pressure, / 10 till further updates.
2023-07-03 fix signedness on a11 message
2023-07-03 ignore negative brake pressure - rethink later.
2023-07-03 Correct node a11 channels and dlc
2023-07-03 brake BAR states for calibrated sensor
2023-07-03 renable a1 message for debug
2023-07-03 Brake balance from 1 bar
2023-07-03 remove brake pressure no data message
2023-07-03 Disable adcdebug, add define to ecu.h
2023-07-05 Tsal set power on, Enable putty debug menu only for config option
2023-07-05 pnode 36 back to data can
2023-07-05 change inverter 1 id from 2 to 1
2023-07-05 removed SDC display in ts active, non active inputs.
2023-07-05 switch ivt u1/u2 meaning on 23
2023-07-05 bms temporary timeout
2023-07-05 brakelight/accu PN changes
2023-07-05 Matlab full bypass path
2023-07-05 lower rtdm brake pressure
2023-07-05 lower brake pressures more, disable matlab, remap inputs agian.
2023-07-05 add rtdm specific brake check
2023-07-05 fixed rtdm brake pressure check
2023-07-05 added pre operation button debug
2023-07-05 add wait precharge debug message on early activation
2023-07-06 Bigger inv conf queue buffer, fix activeprocess comp err
2023-07-06 Ignore i2c transmit errors for test
2023-07-06 reduce update speed further
2023-07-07 Add option of uart 7 for debug, fix a crash if accel curve changed without configs present.
2023-07-07 Treat passive error as canbusdown
2023-07-08 Add ts activation precharge printout
2023-07-08 Add eeprom reset code
2023-07-08 Disable matlab code, fix compile
2023-07-08 calibinfo debug, more pedal msgs, remove interpolation change
2023-07-08 Manual calibration
2023-07-08 r pedal
2023-07-08 fix range check
2023-07-08 direct torque request and rpm
2023-07-08 fix compile
2023-07-08 Undo bypass of doVectoring
2023-07-09 adc read debug, regen range fix, eeprom header set
2023-07-09 non calibrated pedals read 0
2023-07-09 Run adcsetup after debugconf
2023-07-09 move pnode35 to inv can
2023-07-09 Fix debug error spamming when no canbus connected
2023-07-10 Send inverter messages slightly later
2023-07-10 Try clearing txdone queue before waiting
2023-07-10 TWOWHEELS define, setting rear as inverter 1 and 2 motors
2023-07-10 Only register messages for used inverters
2023-07-10 Fix typo on eeprom reset that left only motor 1 enabled
2023-07-11 Fix maxspeed to eeprom, limit to low value on no torque req
2023-07-11 Test
2023-07-11 Adjust timing
2023-07-11 More tweaks
2023-08-01 Use DO15 for SDC control on 23
2023-08-03 fix compile on cube 1.13
2023-08-15 powernode changes in FSG
2023-08-16 Restore debug output
2023-08-16 Switch BMS check to devicestate
2023-08-16 Add regen brake light trigger
2023-08-18 IMD led and BMS led latch
2023-08-18 Fix motorcount check on inverterstatus
2023-08-18 TORQUE_DIFFERENCE define
2023-08-18 Setup left pedal as primary APPS
2023-08-18 New bpsenssor values
2023-08-18 Regen matlab enable config read
2023-08-19 Progress motor operational state in 500ms increments to help diagnose issue, print debug on reaching state
2023-08-19 More options to rpmvals and regenvals
2023-08-19 ensure inverter 0 has time delay set
2023-08-19 Update try to staggered inverter operational bringup
2023-08-19 More debug messaging on operational state request
2023-08-19 Shorten message
2023-08-19 changetime order fix
2023-08-19 fix message len
2023-08-19 Make TIMEINVSTATECHANGE delay value
2023-08-19 debug message on setting inverter change request
2023-08-19 Error location print to debug
2023-08-19 swap IMD/BMS inputs
2023-09-11 disabled PowerNode35 and connected pumps and fans directly to 24v
2023-09-15 commented hack from earlier
2023-09-16 revert debug output
2023-09-16 Fix AllowRegen not being set true, config minimum level
2023-09-16 Store critical error code to errorreason
2023-09-16 fix criticalerror store
2023-09-17 More Config options
2023-09-17 More Cofig opttions
2023-09-17 Allow regen input into dovectoring 21, pass back unchanged.
2023-10-14 Add pedal position to vectoring process
2023-10-16 Fix torquevectoring update activation logic
2023-10-16 Set torque feedback and fwd options actually configurable
2024-01-13 Removed all references to SOC and Siemensinverter
2024-01-18 Removed all references to HPF19, STMADC, and LCD. Sick Encoder only worked with HPF19 so was also removed entirely.
2024-01-23 Removed SPI pins and regenerated code
2024-03-20 added CMAKE
2024-03-20 removed adc
2024-03-21 CMAKE file fix and sendinding debug msg over can bus
2024-03-24 removed adc handlers
2024-04-07 removed outdated systems
2024-04-07 intermediate update
2024-04-21 continuation
2024-05-05 fixed ADC related errors
2024-05-05 more fixes
2024-05-09 intermediate foxes
2024-05-14 intermediate commit
2024-05-23 further commits
2024-05-31 Revert "intermediate commit"
    This reverts commit 0994bf8fea2e9faf952a76d2cc79dc04dd30f745.
2024-06-01 updated torque control
2024-06-10 inter commit
2024-06-11 ignore some safety checks
2024-06-12 Create dbc file
2024-06-13 some cuts
2024-06-14 inverter dbc file
2024-06-14 moved inverters to can 1
2024-06-18 removing extra power stuff
2024-06-18 more cleaning
2024-06-30 working inverters
2024-07-06 updated dbc
2024-07-07 powernode update
2024-07-09 some updates
2024-07-14 more updates
2024-07-17 inverter rear only inverters bug fix
2024-07-17 inverter fix
2024-07-22 changed inverter on state rule
2024-07-31 updated starting sequence
2024-08-06 some cleaning
2024-08-06 new starting sequence
2024-08-06 "Supposedly working" CAN config selection
2024-08-11 semi working code
2024-08-30 bms inverter and pwm updates
2024-08-30 power balance
2024-12-16 Some changes idk what they do
2025-01-08 Delted unused code and some functionality that needs to be brought back in the future. **UNTESTED**.
2025-03-27 PI controllers for fans and coolant pumps have been added
    The new variable WaterTemp has been added to the CarStateType structure. Currently, there is no water temperature sensor, so the controllers cannot be used.
    The controllers have been added to the existing temp_ctl() function in power.c. The old code of the function has been commented out in case it is needed in the future, and it can be removed after the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
2025-10-08 reverted previous tabular changes
2025-10-11 added issue.md to track what needs to be done
2025-10-19 updated information on the components
2025-10-19 added an empty base to remake can2.dbc
2025-10-23 added: components and general errors to the can2 database remake
2025-10-23 missing: analognode not implemented at all in the remake
2026-01-17 \cosmetic changes
    Removed some of the unnecessary code
2026-05-14 compile_commands.json
2026-06-08 compile commands
2026-06-08 included the correct FreeRTOS header file
2026-06-08 WIP can bus menu
2026-06-08 mapped out basic issues with configuration file
2026-06-08 trying to fix EEPROM's enqueue not being processed
2026-06-08 EEPROMTask template skeleton
2026-06-11 added fullsave to CAN config changer
2026-06-14 testing
2026-06-17 added header to eeprom.h
2026-06-22 changed header values
2026-06-22 fixed task handler and changed variable names
2026-06-22 added some necessary startup options to realmain
2026-06-22 updated commit function to check if device is ready
2026-06-22 minor fixes to header file
